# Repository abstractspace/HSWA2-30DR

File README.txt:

This is a RF switch using the HSWA2-30DR+
The sma connectors used are: 
931-1175-ND  https://www.digikey.com/products/en?keywords=931-1175-ND
CONSMA013.062-ND  https://www.digikey.com/products/en?keywords=CONSMA013.062-ND

You should have everything needed to open it in KiCad within the RF_Switch.zip archive. I think the custom library symbols and are included here as well.

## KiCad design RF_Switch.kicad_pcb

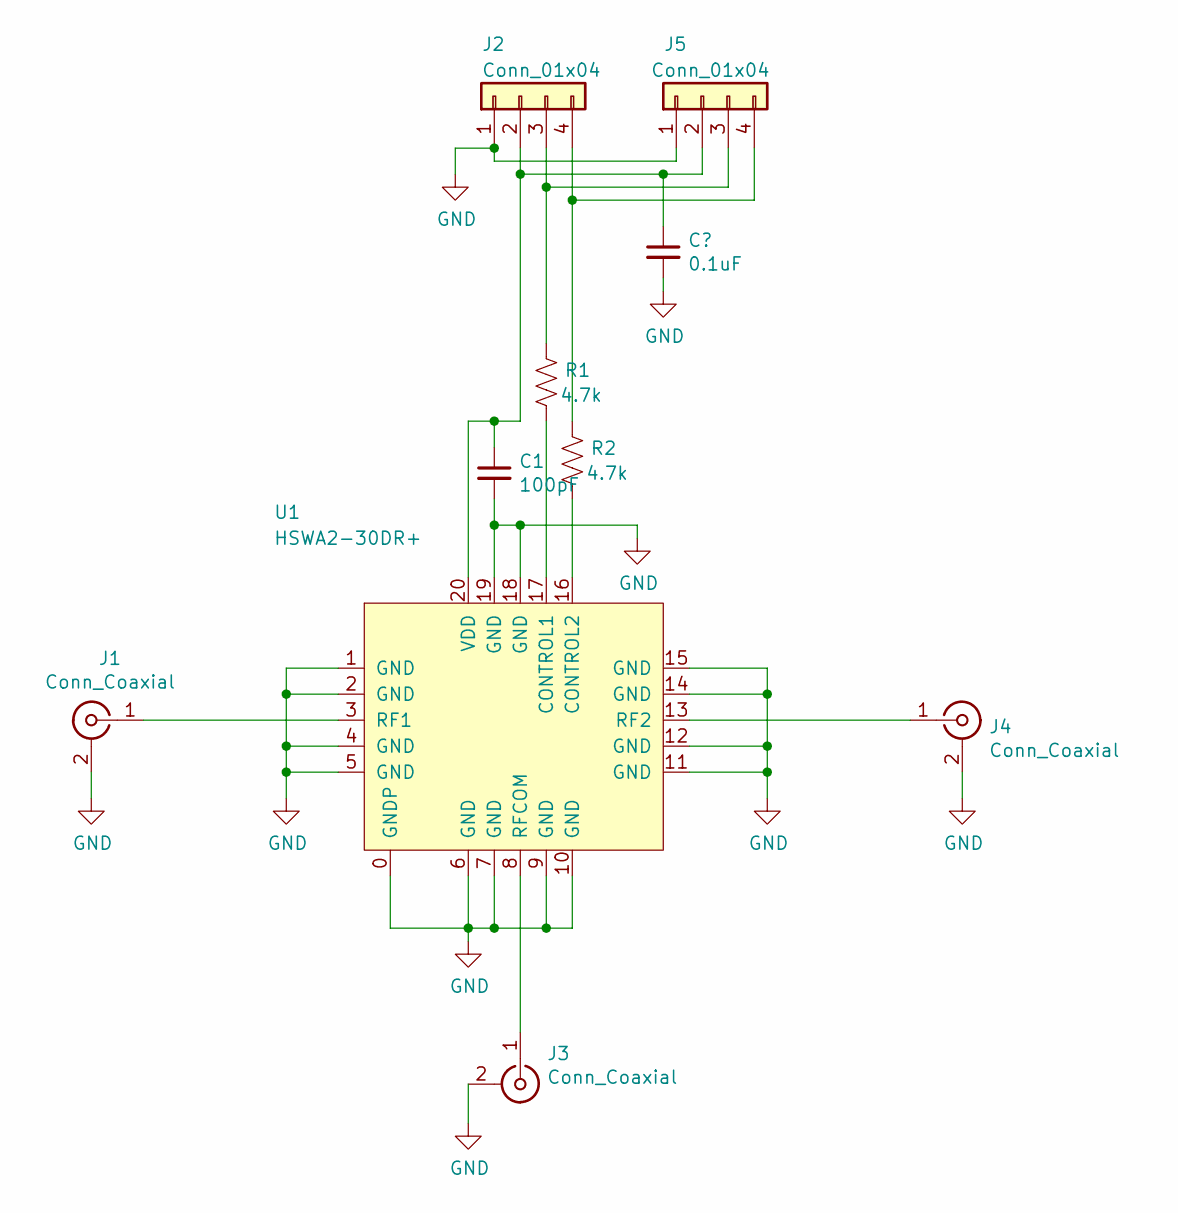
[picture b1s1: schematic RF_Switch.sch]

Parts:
C1: 100pF; C_0603_1608Metric
J1, J4: Conn_Coaxial; SMA_Taoglas_Limited_Narrow_EdgeMount; Digikey Part Number 931-1175-ND
J2, J5: Conn_01x04; Header 4 Keyed RT Angle
J3: Conn_Coaxial; SMA_Plug_Linx_Technologies_EdgeMount_CONSMA013.062; Digikey Part Number CONSMA013.062-ND
R1, R2: 4.7k; R_0603_1608Metric
U1: HSWA2-30DR+

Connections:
GND: C1.2, J1.2 (Ext), J2.1, J3.2 (Ext), J4.2 (Ext), J5.1, U1.0 (GNDP), U1.1 (GND), U1.2 (GND), U1.4 (GND), U1.5 (GND), U1.6 (GND), U1.7 (GND), U1.9 (GND), U1.10 (GND), U1.11 (GND), U1.12 (GND), U1.14 (GND), U1.15 (GND), U1.18 (GND), U1.19 (GND); also elsewhere on the board
unnamed 1: C1.1, J2.2, J5.2, U1.20 (VDD); also elsewhere on the board
unnamed: J1.1 (In), U1.3 (RF1)
unnamed: J2.3, J5.3, R1.1
unnamed: J2.4, J5.4, R2.1
unnamed: J3.1 (In), U1.8 (RFCOM)
unnamed: J4.1 (In), U1.13 (RF2)
unnamed: R1.2, U1.17 (CONTROL1)
unnamed: R2.2, U1.16 (CONTROL2)

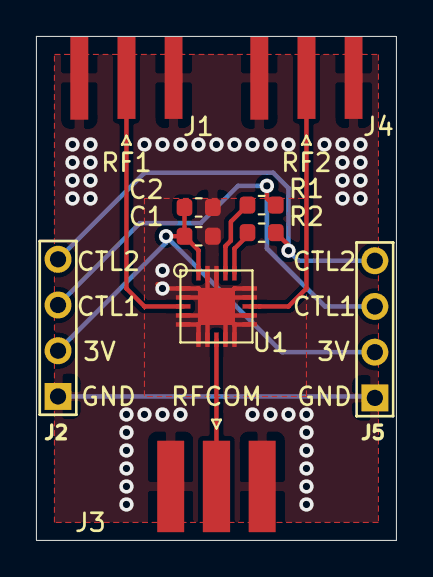
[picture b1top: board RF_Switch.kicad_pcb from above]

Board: 2 copper layers, 20.0 x 28.0 mm, 10 parts (0 on the bottom side), 9 nets.

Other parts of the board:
C2: 0.1uF; C_0603_1608Metric

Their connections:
GND: C2.2; also elsewhere on the board
unnamed 1: C2.1; also elsewhere on the board

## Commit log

2020-05-13 Finished REV A
2020-05-13 Added PDF schematic and README
2020-05-13 Added two vias by the RFCOM port to link top and bottom copper close to this connector
2020-05-13 Updated KiCad archive zip file to newest version
2020-05-13 Added lots of vias to tie top and bottom together better
